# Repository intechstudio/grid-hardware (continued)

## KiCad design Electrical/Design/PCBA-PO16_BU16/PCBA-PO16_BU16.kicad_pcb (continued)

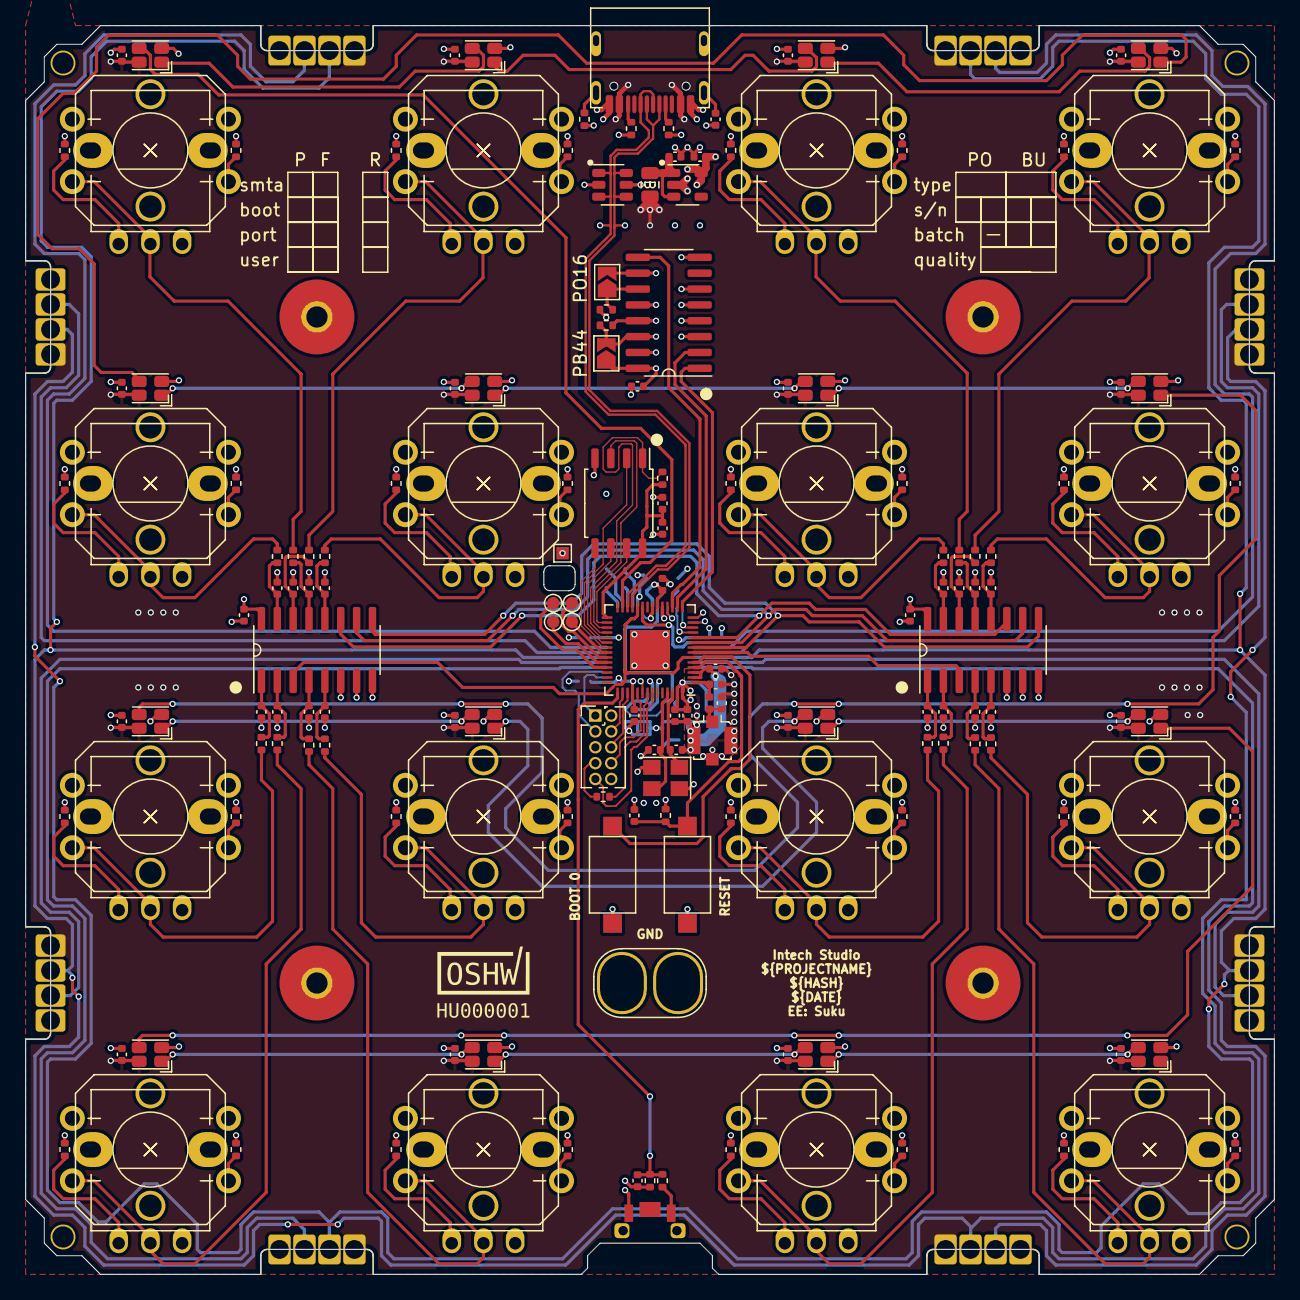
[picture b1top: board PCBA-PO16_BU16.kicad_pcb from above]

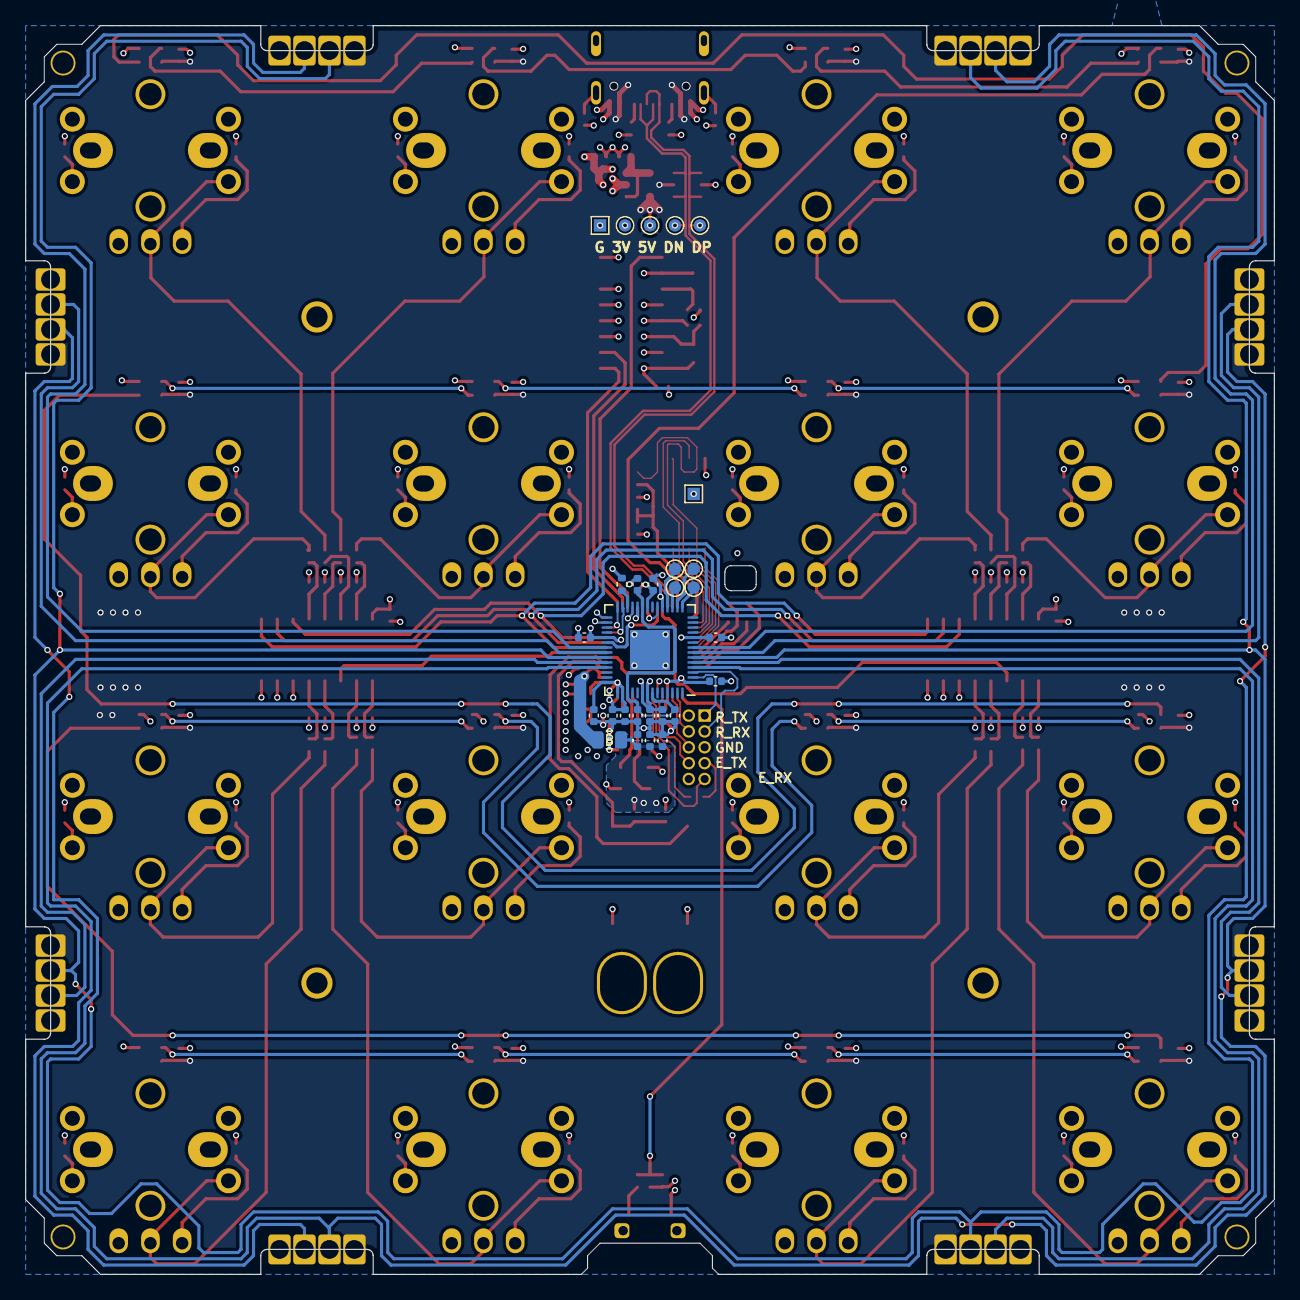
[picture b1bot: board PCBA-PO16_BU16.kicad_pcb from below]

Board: 4 copper layers, 100.0 x 100.0 mm, 219 parts (28 on the bottom side), 153 nets.

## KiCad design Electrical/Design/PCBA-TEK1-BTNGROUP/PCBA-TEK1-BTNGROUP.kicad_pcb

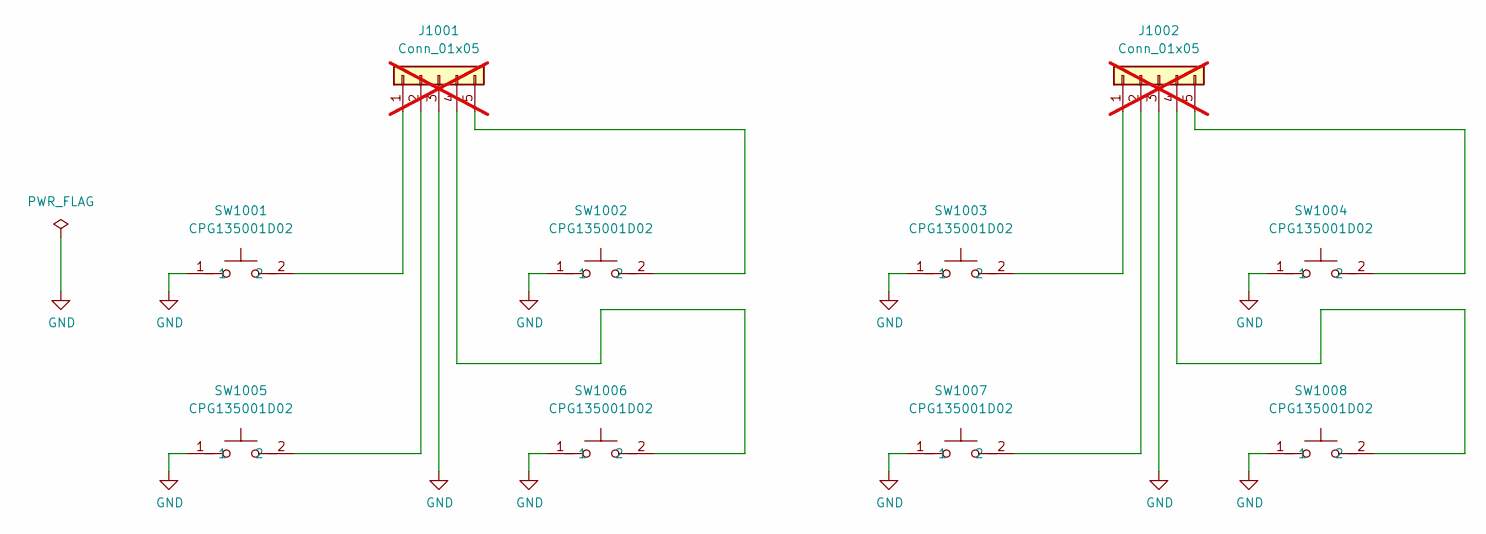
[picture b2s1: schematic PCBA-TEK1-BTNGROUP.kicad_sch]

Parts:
J1001, J1002: Conn_01x05; PinHeader_1x05_P2.54mm_Vertical; not fitted
SW1001, SW1002, SW1003, SW1004, SW1005, SW1006, SW1007, SW1008: CPG135001D02; KEY-TH_CPG135001D0X; LCSC Part C400230

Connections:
GND: J1001.3, J1002.3, SW1001.1, SW1002.1, SW1003.1, SW1004.1, SW1005.1, SW1006.1, SW1007.1, SW1008.1
unnamed: J1001.1, SW1001.2
unnamed: J1001.2, SW1005.2
unnamed: J1001.4, SW1006.2
unnamed: J1001.5, SW1002.2
unnamed: J1002.1, SW1003.2
unnamed: J1002.2, SW1007.2
unnamed: J1002.4, SW1008.2
unnamed: J1002.5, SW1004.2

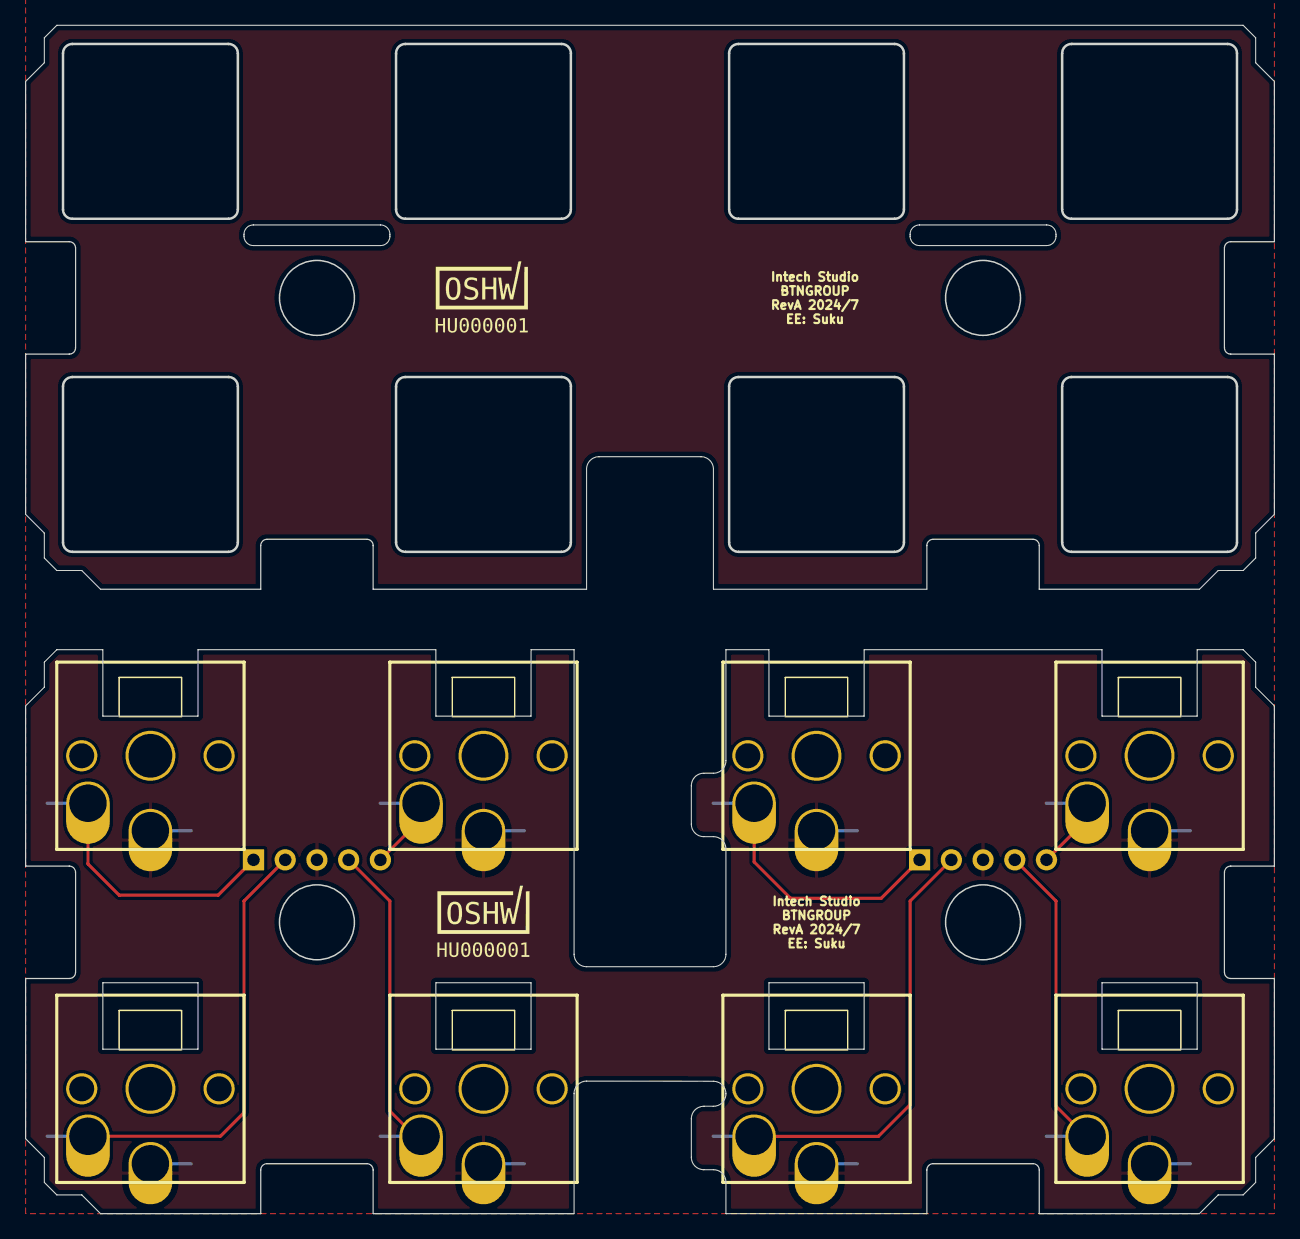
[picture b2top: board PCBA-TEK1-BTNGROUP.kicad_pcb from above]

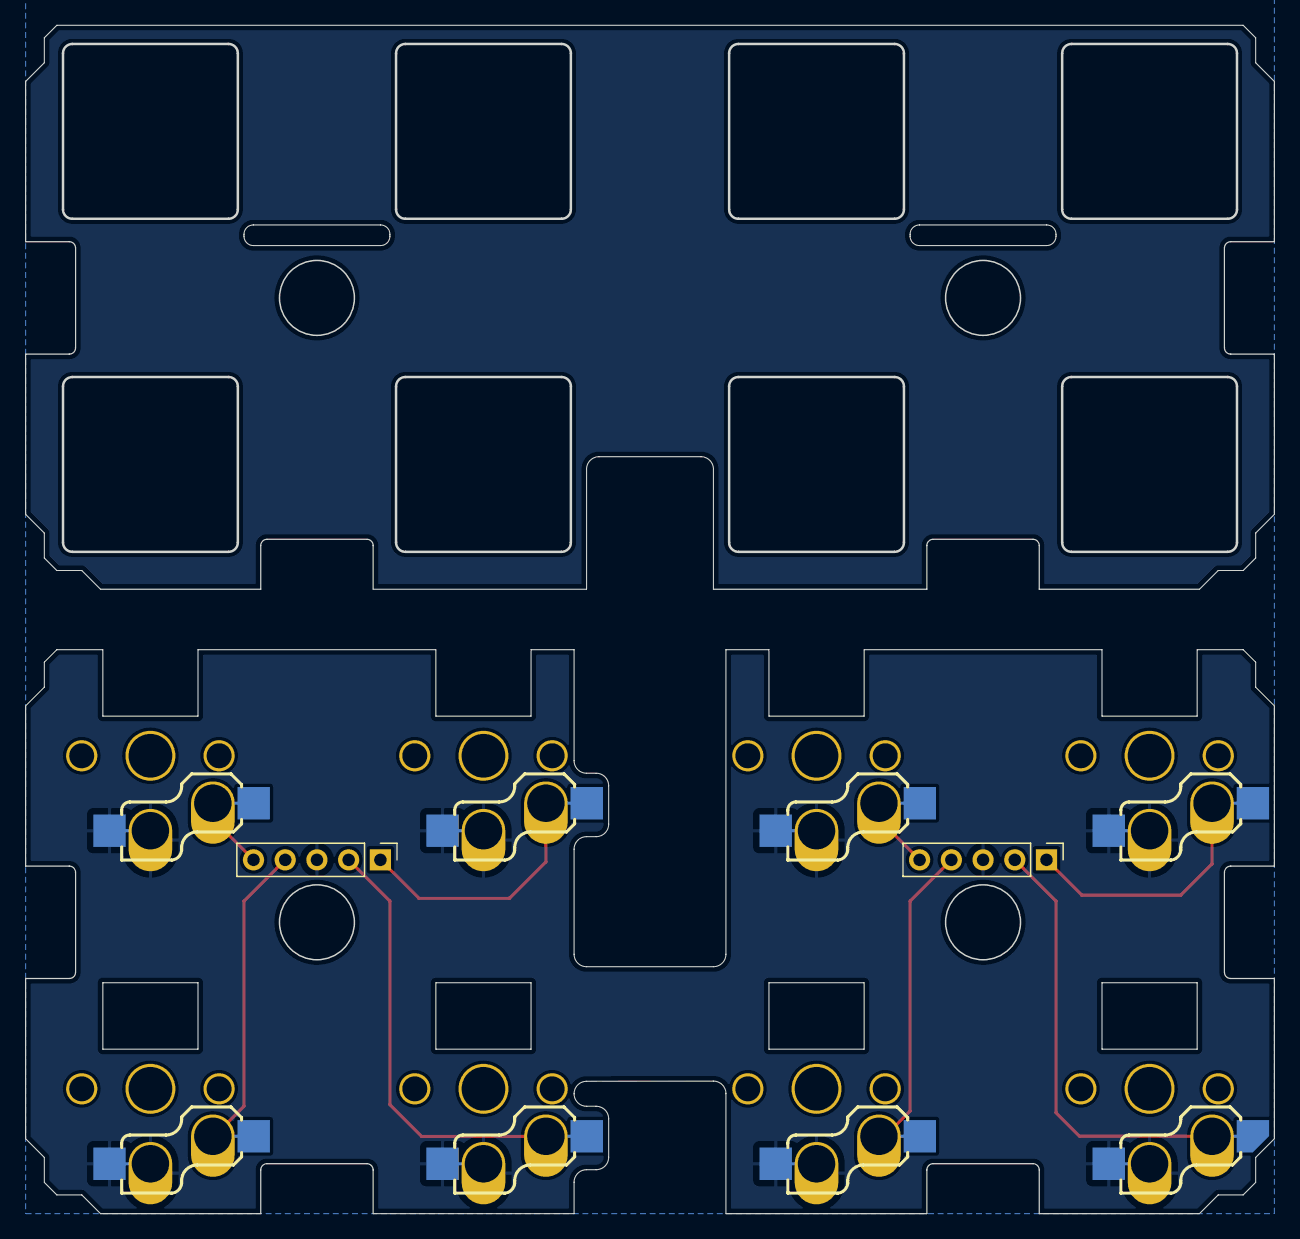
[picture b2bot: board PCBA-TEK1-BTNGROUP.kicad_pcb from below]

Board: 2 copper layers, 100.0 x 45.2 mm, 12 parts (10 on the bottom side), 9 nets.

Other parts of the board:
LOGO701, LOGO701#2: LOGO; OSHWA
